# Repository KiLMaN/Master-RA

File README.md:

Master-RA
=========

This project is part of the french university (Université de Cergy-Pontoise).

The goal of the project is to create a augmented reality game based on a Android smartphone and on a embeded Raspberry Pi

You can see the progress of the project on the website at : http://www.projetra.squadfree.net/

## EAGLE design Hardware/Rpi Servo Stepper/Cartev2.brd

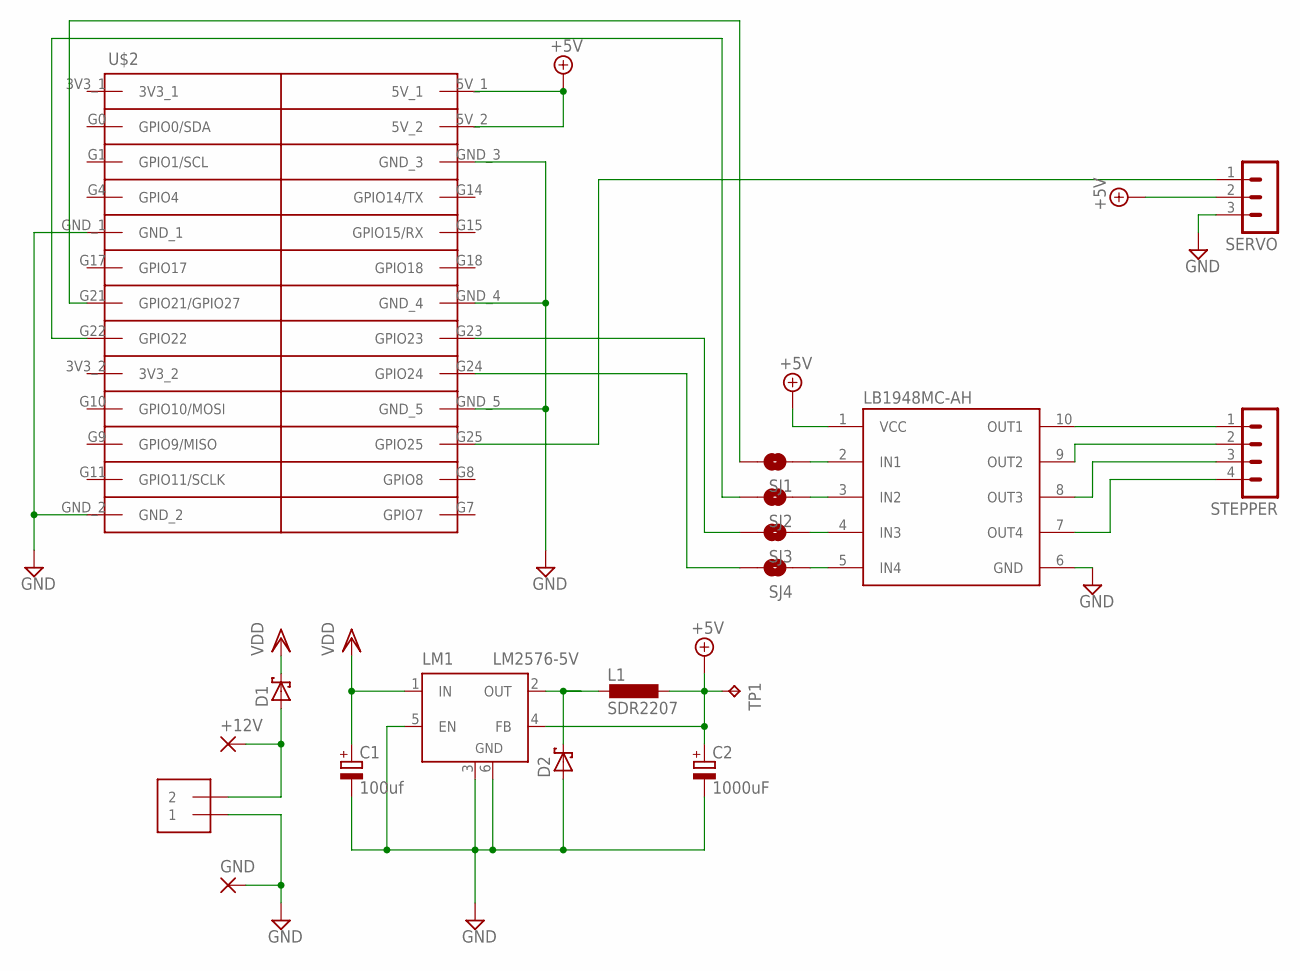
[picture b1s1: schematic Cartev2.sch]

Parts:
+12V: 3,81/1,4
C1: 100uf; PANASONIC_E
C2: 1000uF; PANASONIC_G
D1, D2: SCHOTTKY-DIODESMC; SMC
GND: 3,81/1,4
J1: 1X2-3.5MM; 3.5MMTERM
L1: SDR2207; SM
LB1948MC-AH: LB1948MC-AH; SOIC-10
LM1: LM2576-5V; TO263-5
SERVO: MA03-1
SJ1, SJ2, SJ3, SJ4: SOLDERJUMPERTRACE; SJ_2S-TRACE
STEPPER: MA04-1
TP1: TPTP10SQ; TP10SQ
U$2: CONNECTEUR_RPI; 26PIN

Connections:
+5V: C2.+, L1.P$2 (2), LB1948MC-AH.1 (VCC), LM1.4 (FB), SERVO.2, TP1.TP, U$2.5V_1, U$2.5V_2
GND: C1.-, C2.-, D2.A, GND.1, J1.1, LB1948MC-AH.6 (GND), LM1.3 (GND), LM1.5 (EN), LM1.6 (GND), SERVO.3, U$2.GND_1, U$2.GND_2, U$2.GND_3, U$2.GND_4, U$2.GND_5
unnamed: LB1948MC-AH.10 (OUT1), STEPPER.1
unnamed: LB1948MC-AH.9 (OUT2), STEPPER.2
unnamed: LB1948MC-AH.8 (OUT3), STEPPER.3
unnamed: LB1948MC-AH.7 (OUT4), STEPPER.4
unnamed: +12V.1, D1.A, J1.2
unnamed: D2.C, L1.P$1 (1), LM1.2 (OUT)
unnamed: LB1948MC-AH.2 (IN1), SJ1.1
unnamed: LB1948MC-AH.3 (IN2), SJ2.1
unnamed: LB1948MC-AH.4 (IN3), SJ3.1
unnamed: LB1948MC-AH.5 (IN4), SJ4.1
unnamed: SERVO.1, U$2.G25 (GPIO25)
unnamed: SJ1.2, U$2.G21 (GPIO21/GPIO27)
unnamed: SJ2.2, U$2.G22 (GPIO22)
unnamed: SJ3.2, U$2.G23 (GPIO23)
unnamed: SJ4.2, U$2.G24 (GPIO24)
VDD: C1.+, D1.C, LM1.1 (IN)

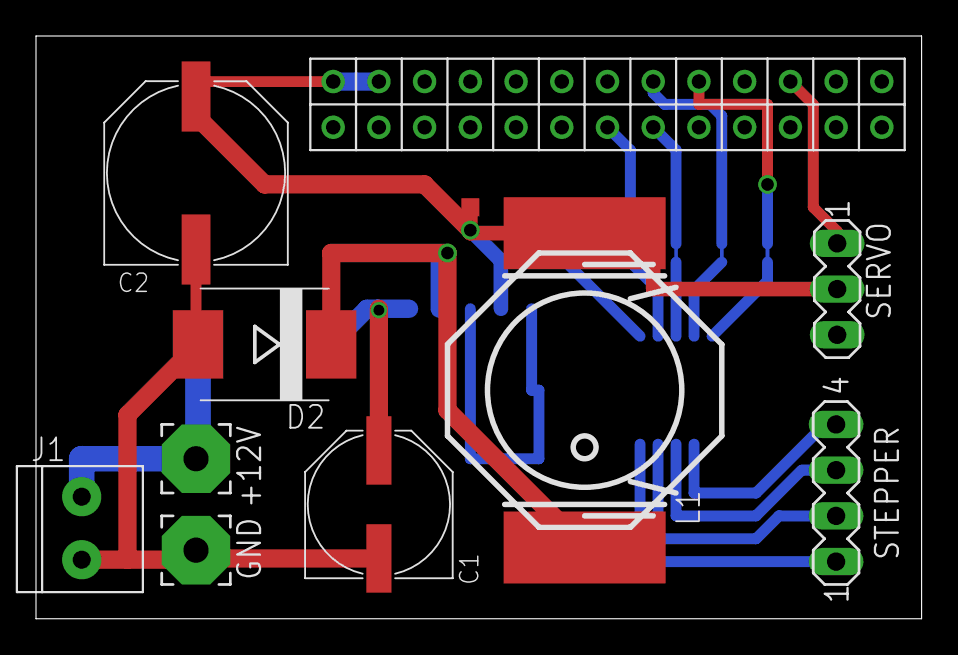
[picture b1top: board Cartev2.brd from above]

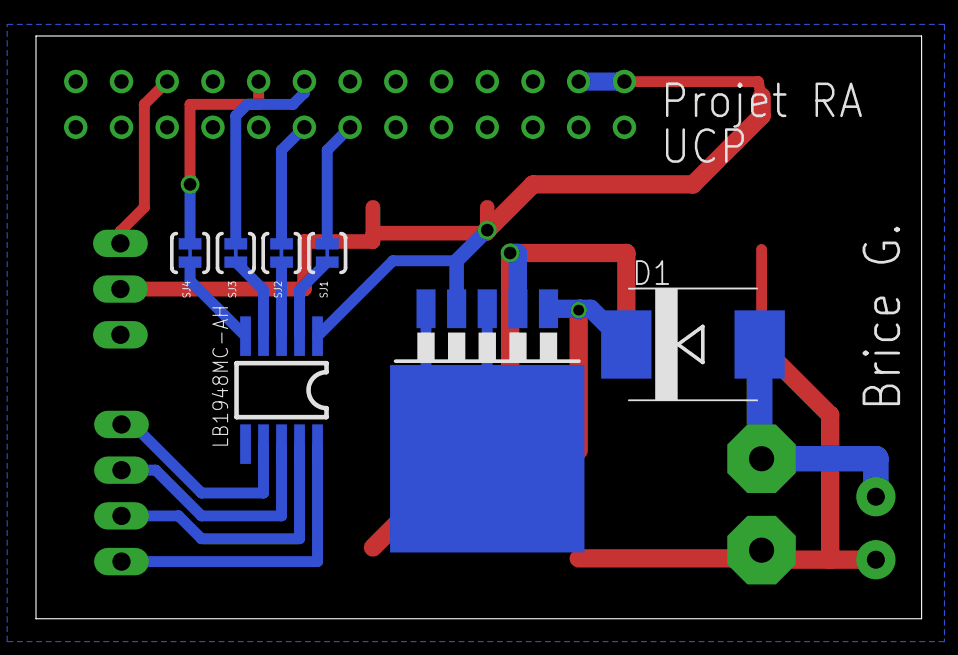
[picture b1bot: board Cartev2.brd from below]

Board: 2 copper layers, 49.2 x 32.4 mm, 18 parts (7 on the bottom side), 18 nets.

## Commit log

2014-01-02 RepoCreate & Hardware
2014-01-15 Hardware V2 PROD
    Version ITEAD Studio Production
2014-02-27 Create Android TCP/UDP Server
2014-02-27 Adding source of the embeded software
2014-02-27 Move Embeded software
2014-02-27 Rename INTALL.README.MD to README.md
2014-02-27 Add source to access Android camera service
2014-03-03 update gstreamer
2014-03-03 adding config eclipse
2014-03-05 Create File for Raspberry Configuration IP
2014-03-26 Update gitIgnore to keep eclipse conf
2014-03-26 Hardware update
2014-03-26 Create GameplaySimu
2014-03-26 Creation des différents packages et des différentes classes
2014-03-26 Ajouts des différents attributs de chaque objets
2014-03-26 ajout des constructeurs et des getters/setters
2014-03-30 Creation de certaines classes
2014-03-30 Modification de Position avec creation d'une classe Attention, classe Tower incorrecte
2014-03-30 Create Files for TCP server Raspberry
2014-03-30 Debut Gameplay, fonctionnel sur PC Encore beaucoup à faire mais le debut est là ;)
2014-03-30 Enemies => Enemie
2014-03-31 Adding Pathing for the enemies, need to folow the path now
2014-03-31 XML Configuration of the waves and towers
2014-03-31 Removing Debug and update follower
2014-03-31 Test Android OK ;)
2014-03-31 config xml files
2014-04-01 Add XML config for weapons Add interface for supporting xml file in Android prject
2014-04-02 Ajout de commentaires
2014-04-09 Ajout de la classe Pweapon et modification des classes qui sont affectées par ce changement
2014-04-28 Gestion des points du joueur ajouté
2014-04-30 Gestion des vies du joueur
2014-04-30 Gestion des vies du joueur + Probabilité d'atteindre un ennemi
2014-05-02 Ajout de AndEngine + Intégration menu
2014-05-02 Remove Unused Assets
2014-05-02 Removing border glitch
2014-05-02 Update Clear Project
2014-05-04 Ajoute programme embarqué
2014-05-07 Fix missing DEBUG
2014-05-07 Correction Debug => Debuging
2014-05-07 gestion des pauses de la partie + changement possibles des positions tours pendant les pauses
2014-05-07 Ajout du controle de la tour avec le joystick
2014-05-07 Adding Andar And switch to android 16
2014-05-07 FUCK GIT
2014-05-07 Ajout de l'affichage des points de vie Ajout de l'image de l'image settings
2014-05-07 Ajout image settings
2014-05-07 android16
2014-05-07 Remove error OpenGL ES2
2014-05-08 Remove AndAR and adding Rajawali for 3D models
2014-05-08 Remove Unused Examples
2014-05-08 Ajout de Gstreamer
2014-05-08 Update to compile without Gstreamer
2014-05-08 Adding JavaDoc, and cleanup some mess
2014-05-08 Remove useless classes
2014-05-08 ajout de cliquable play et cliquable settings
2014-05-08 Adding lib to handle image Data and test it ;)
2014-05-09 Remove unused OnPreviewFrame
2014-05-09 Github changes
2014-05-09 no message
2014-05-09 Sobel Edge detection
2014-05-14 armes améliorées (distance,temps de chargement) + armes débloquées en fonction de leurs usages + le joueur peut prendre le contrôle d'une tour
2014-05-14 Ajout d'attributs dans GameGonfig et GamePanel
2014-05-21 Modification de Jini pour Gstreamer
2014-05-21 Create new branche
2014-05-21 Artoolkit in java
2014-05-21 Fuck la polise
2014-05-27 changement interface graphique
2014-05-28 GST working
2014-05-28 touche du bouton play vu comme un clique
2014-05-28 fin de mise en place des boutons des tours
2014-05-29 Working AR detection
2014-05-29 Gstreamer Changement IP OK
2014-05-29 Add Gstreamer on GameActivity
2014-06-01 Working multiple marker detection
2014-06-03 Intégration boutons des tours et de la tablette
2014-06-03 Correction d'un bug sur deux lié au bouton pause.
2014-06-04 ScreenShoot RA
2014-06-04 ajout des 3/4 de tools
2014-06-04 Working IHM
2014-06-04 Cleanup GPU IMAGE
2014-06-04 Commit before merge RA
2014-06-04 Start Merge
2014-06-04 Ca fonctionne !
2014-06-04 New version of the upgrade system
2014-06-04 Gstreamer Multi Source
2014-06-04 joystick ok
2014-06-04 Ajout Udp autodetection
2014-06-04 Prepare merge gst
2014-06-04 merge
2014-06-04 changement des images des tours et de la tablette
2014-06-04 reduction police Tools + positionnement nom et état
2014-06-04 Meme resolution sur tout les appareils, tentative de debloquage GST
2014-06-16 Update page d'upgrade des tour, fonctionne ;)
2014-06-17 Working Tower detection
2014-06-17 Tower control and selection ok
2014-06-17 Detection Tour, connexion control et connexion GST ok Déconection GST a faire !
2014-06-18 Correction Affichage cameras
2014-06-20 Working AR
2014-06-20 Mise à jour des textes en francais. Modification de la page de démarrage
2014-06-20 noname
2014-06-20 Fixed Credit
2014-06-20 Mise à jour des icones
2014-06-21 TopDownView ok
2014-06-22 New working detection of types
2014-06-22 Working ;)
2014-06-23 Work
2014-06-26 1ere correction du bug
2014-06-26 Correctif Auto-detection et controle multi-tour
2014-06-26 Tower POV
2014-06-26 RA tower
2014-06-26 presque enemis
2014-06-26 tentative pour ne plus voir le joystick entre le passage d'une scene à une autre

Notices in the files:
parts and their libraries:
SparkFun-Passives: Licensing: CC v3.0 Share-Alike You are welcome to use this library for commercial purposes.
